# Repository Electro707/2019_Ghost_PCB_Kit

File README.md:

# 2019_Ghost_PCB_Kit
This is a sodlering kit of a ghost, designed for one of many UNH Makerspace's events

This repository is archived, as it's a one-time design.
Now files are hosted on Google Drive.

Link to website, in which the Google Drive link can be found:
[Link](https://electro707.com/documentation/PCB/2019_Ghost/index.php)

I may create a new general reposity for the kit that will be updated as time goes on 
(there also won't be any of the University of New Haven logos on that one).

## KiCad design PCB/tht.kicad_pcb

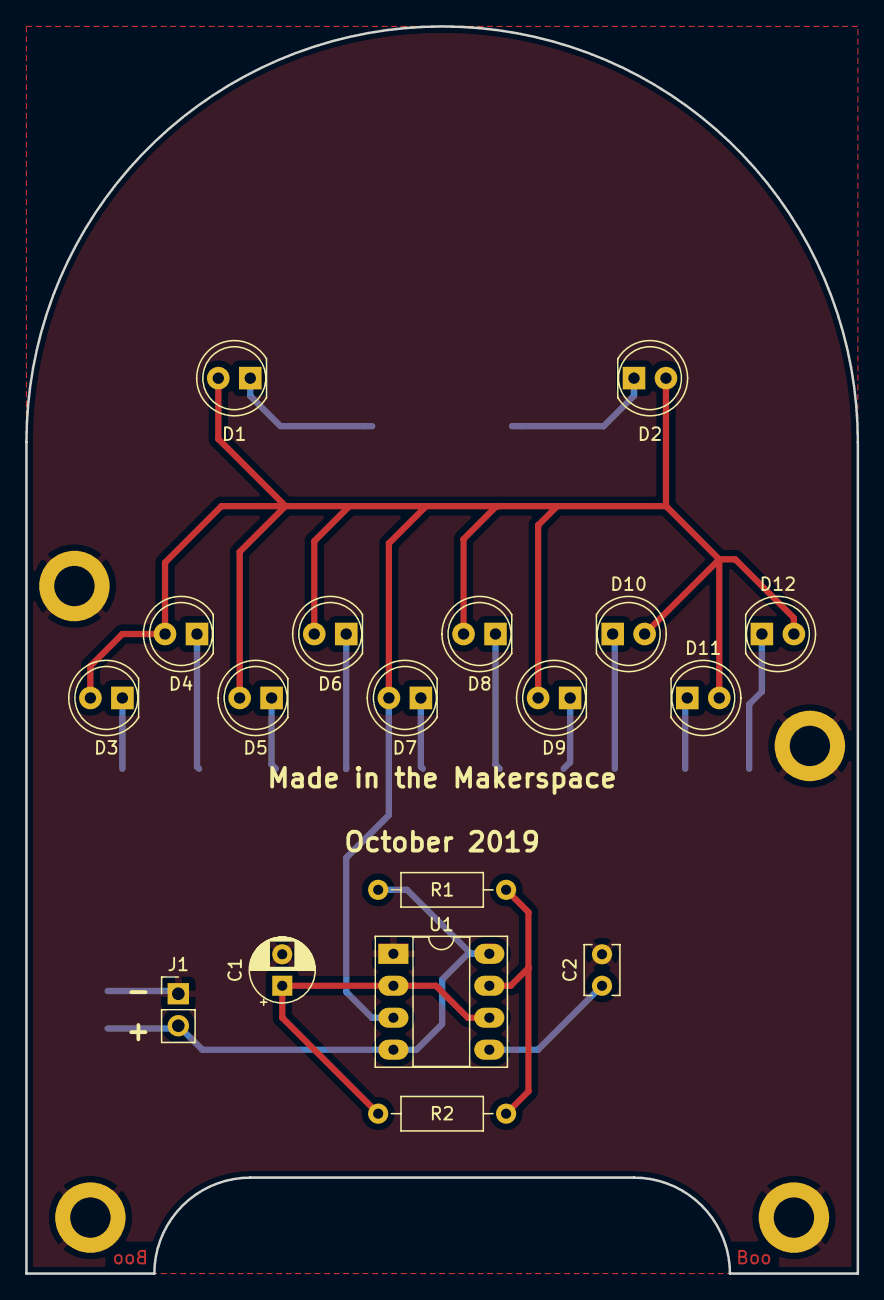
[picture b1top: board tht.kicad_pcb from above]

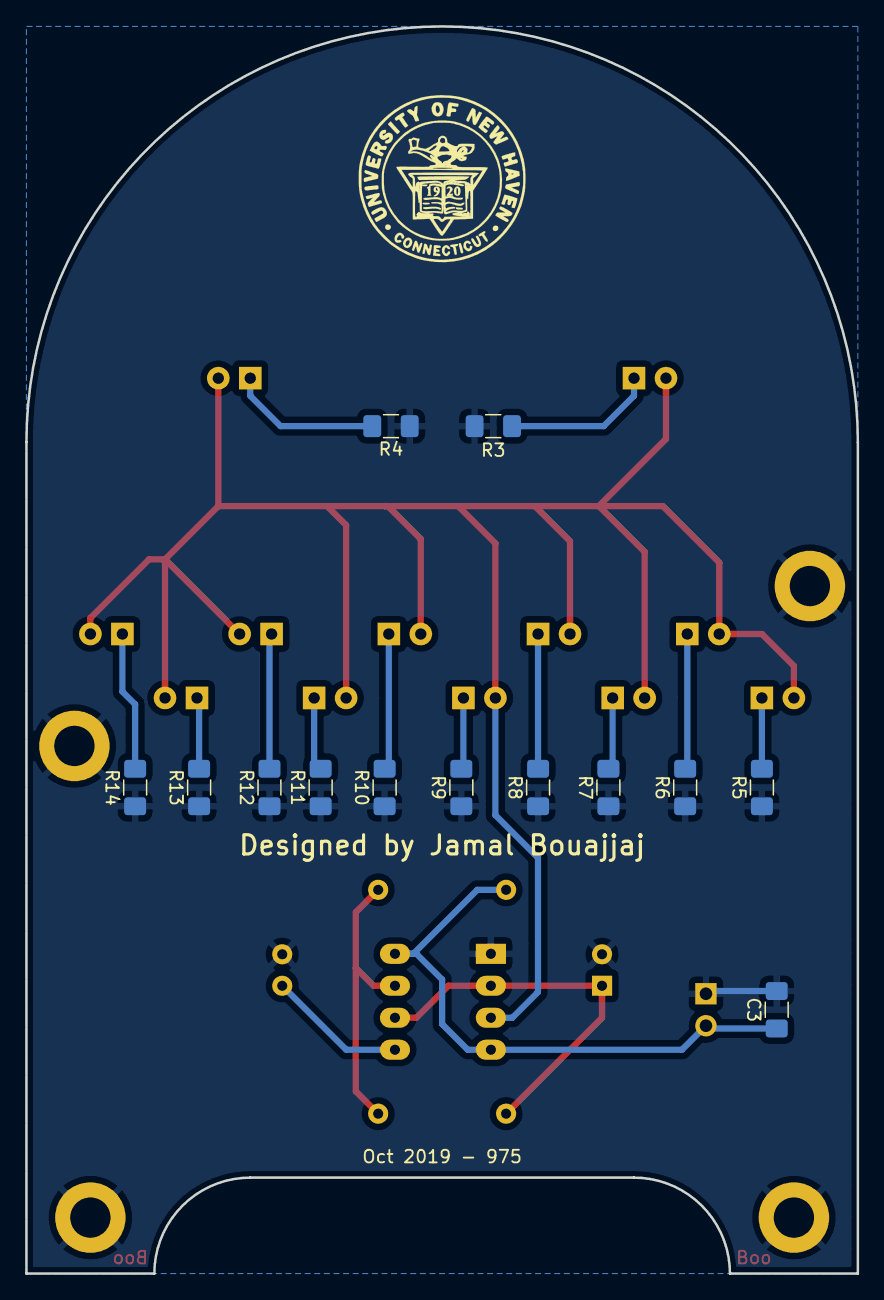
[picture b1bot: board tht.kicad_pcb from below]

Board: 2 copper layers, 66.0 x 99.1 mm, 35 parts (13 on the bottom side), 18 nets.

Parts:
C1: C; CP_Radial_D5.0mm_P2.50mm
C2: C; C_Disc_D3.8mm_W2.6mm_P2.50mm
C3: 1uF; C_1206_3216Metric_Pad1.42x1.75mm_HandSolder
D1, D2, D3, D4, D5, D6, D7, D8, D9, D10, D11, D12: LED; LED_D5.0mm
H1, H2, H3, H4: 3.2mm Mounting Hole; MountingHole_3.2mm_M3_DIN965_Pad
J1: Conn_01x02; PinHeader_1x02_P2.54mm_Vertical
R1, R2: R; R_Axial_DIN0207_L6.3mm_D2.5mm_P10.16mm_Horizontal
R3, R4, R5, R6, R7, R8, R9, R10, R11, R12, R13, R14: 330; R_1206_3216Metric_Pad1.42x1.75mm_HandSolder
U1: LM555; DIP-8_W7.62mm_Socket_LongPads

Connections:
GND: C1.2, C2.2, C3.2, H1.1, H2.1, H3.1, H4.1, J1.1, R3.1, R4.1, R5.1, R6.1, R7.1, R8.1, R9.1, R10.1, R11.1, R12.1, R13.1, R14.1, U1.1
unnamed: C1.1, R2.1, U1.2, U1.6
unnamed: C2.1, U1.5
unnamed: D1.1, R3.2
unnamed: D1.2, D2.2, D3.2, D4.2, D5.2, D6.2, D7.2, D8.2, D9.2, D10.2, D11.2, D12.2, U1.3
unnamed: D2.1, R4.2
unnamed: D3.1, R5.2
unnamed: D4.1, R6.2
unnamed: D5.1, R7.2
unnamed: D6.1, R8.2
unnamed: D7.1, R9.2
unnamed: D8.1, R10.2
unnamed: D9.1, R11.2
unnamed: D10.1, R12.2
unnamed: D11.1, R13.2
unnamed: D12.1, R14.2
unnamed: R1.1, R2.2, U1.7
VCC: C3.1, J1.2, R1.2, U1.4, U1.8

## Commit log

2020-04-16 Pre-Archive Change
